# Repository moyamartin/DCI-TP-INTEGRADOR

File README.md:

## Trabajo práctico final de la asignatura DCI ##
Este repositorio contiene el trabajo práctico final para la asignatura de Diseño de Circuitos Impresos de la carrera de posgrado de FIUBA.

* Autor: Martin Moya
* Título corto del trabajo: Módulo PPG MAX30101
* Descripción: Rediseño miniaturizado del módulo MAX30101 de MikroElektronika (sensor óptico de pulso y oximetría PPG) para su integración en un reloj. El objetivo es reducir el tamaño de la placa conservando la función de medición de frecuencia cardíaca y SpO2 por I2C.
* Cursada: OCT-NOV-DIC 2026

## Licencia de este trabajo ##
Este trabajo se distribuye bajo la licencia de hardware abierto CERN-OHL-P v2 (CERN Open Hardware Licence Version 2 - Permissive).
El texto de la licencia debe colocarse en el directorio raíz (LICENSE).

## Estructura del TP FINAL ##

Se propone y se pide utilizar la siguiente estructura.

* doc: Toda la información sobre el circuito, principalmente de autoría o procesamiento propio. Por ejemplo:
  * Notas de ingeniería propias.
  * Notas de aplicación propias.
  * Estudios previos, estado del arte, resumen de las investigaciones.
  * Notas con cálculos.
  * Dibujos adicionales.
  * Fotos de los prototipos.
  * Presupuestos, cotizaciones.
* info: Toda la iformación recolectada, principalmente de terceros, como por ejemplo:
  * Hojas de datos.
  * Notas de aplicación.
  * Info de productos comerciales.
  * Info en internet.
* pcb: Archivos de diseño esquemático y pcb.

Dependiendo la magnitud del proyecto, tendremos más o menos información en estos directorios. 
Revisar los README.md en cada directorio para conocer las pautas de cada uno para este TP.

NOTA: El alumno puede y debe borrar de este archivo todo lo que considere necesario, por ejemplo las aclaraciones del docente y esta misma nota.

## Obligatorios para el TP Final ##
* doc/propuesta/README.md (con textos y links, formato markdown, a imágenes que deben estar en el mismo repo. Las imágenes son las que se piden en las pautas de TP).
* info/*.pdf (Se piden solo las hojas de datos de los componentes relevantes como circuitos integrados, conectores particulares, módulos, etc. No es necesario poner hojas de pasivos, discretos comunes, conectores estándar.)
* pcb/* (Acá va el proyecto KiCad, modelos 3D, bibliotecas particulares y archivos generados como BOM, gerbers, etc.). EVITE subir al git archivos temporales de KiCad. Se recomienda usar un .gitignore adecuado.
* El alumnos es libre de agregar otras cosas, pero siempre tenga en cuenta que el repositorio es público. Evitar colocar información personal o documentación confidencial.

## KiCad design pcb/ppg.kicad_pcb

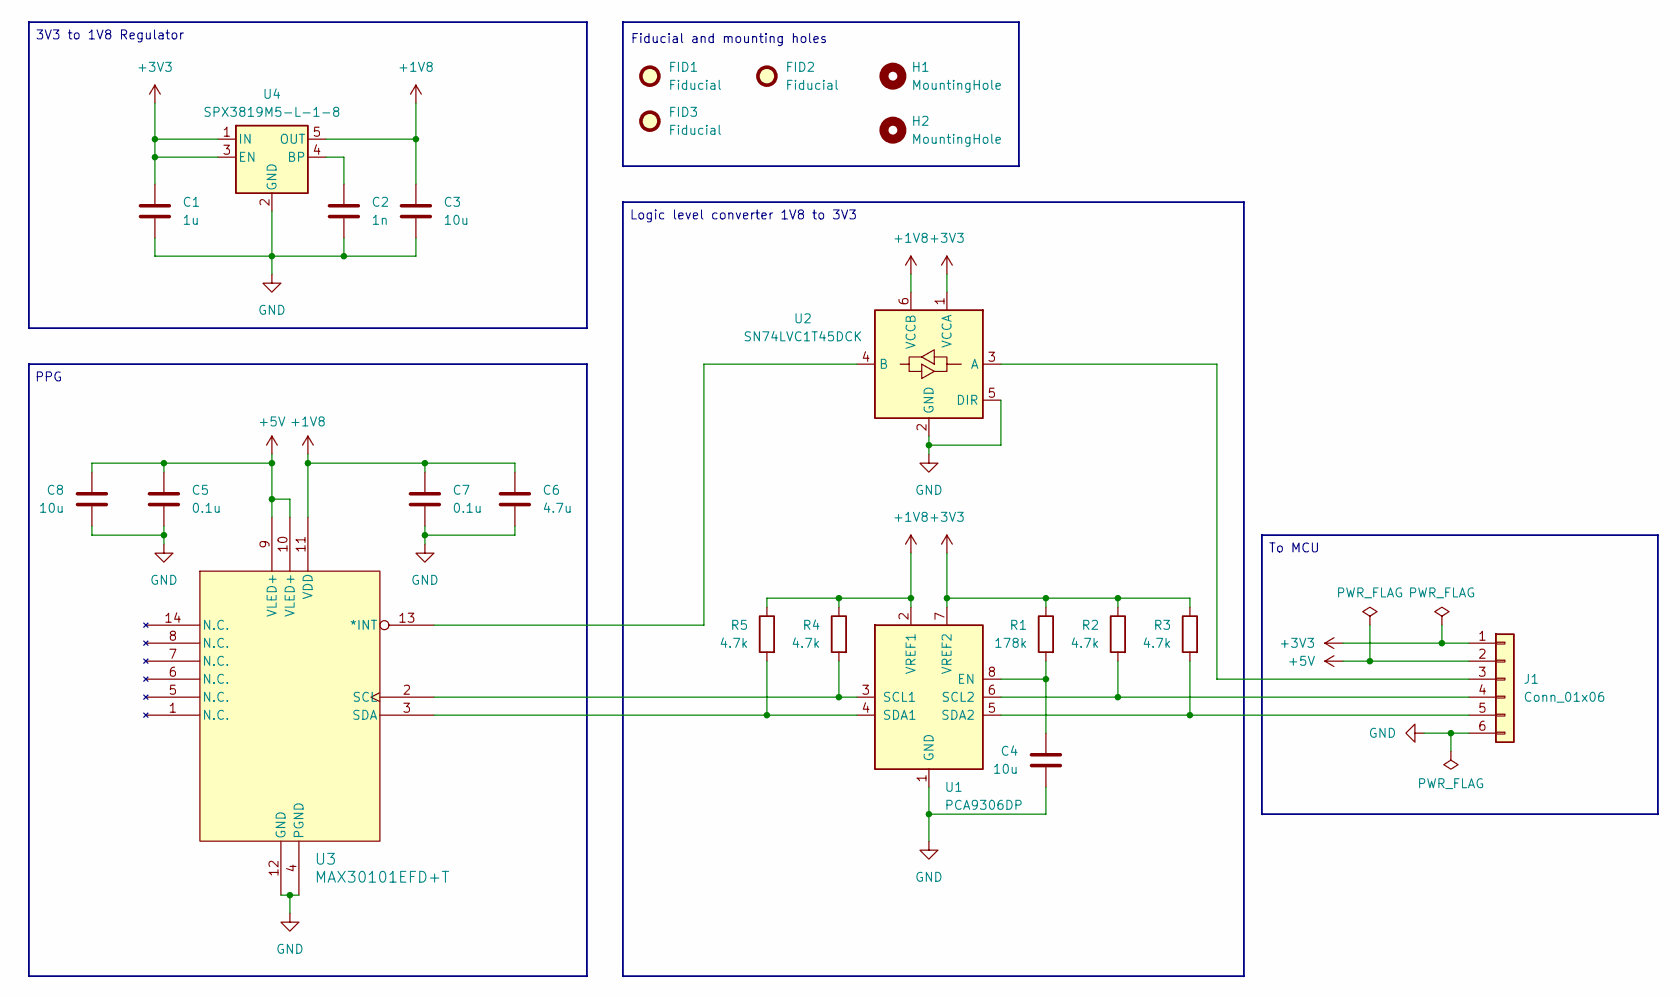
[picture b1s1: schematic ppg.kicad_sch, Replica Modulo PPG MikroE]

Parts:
C1: 1u; C_0603_1608Metric_Pad1.08x0.95mm_HandSolder; digikey# 399-C0603C104K5RACTUCT-ND
C2: 1n; C_0603_1608Metric_Pad1.08x0.95mm_HandSolder; digikey# 399-C0603X102K5RAC3316CT-ND
C3: 10u; C_0603_1608Metric_Pad1.08x0.95mm_HandSolder; digikey# 718-2355-1-ND
C4, C8: 10u; C_0603_1608Metric_Pad1.08x0.95mm_HandSolder; digikey# 1276-1869-1-ND
C5, C7: 0.1u; C_0603_1608Metric_Pad1.08x0.95mm_HandSolder; digikey# 399-C0603C104K5RACTUCT-ND
C6: 4.7u; C_0603_1608Metric_Pad1.08x0.95mm_HandSolder; digikey# 490-7203-1-ND
FID1, FID2, FID3: Fiducial; Fiducial_1mm_Mask2mm
H1, H2: MountingHole; MountingHole_2.1mm
J1: Conn_01x06; Molex_200528-0060_1x06-1MP_P1.00mm_Horizontal; digikey# WM24188CT-ND
R1: 178k; R_0603_1608Metric_Pad0.98x0.95mm_HandSolder; digikey# RMCF0603FT178KCT-ND
R2, R3, R4, R5: 4.7k; R_0603_1608Metric_Pad0.98x0.95mm_HandSolder; digikey# 311-4.70KHRCT-ND
U1: PCA9306DP; TSSOP-8_3x3mm_P0.65mm; digikey# 568-4243-1-ND
U2: SN74LVC1T45DCK; SOT-363_SC-70-6; digikey# 296-16844-1-ND
U3: MAX30101EFD+T; 21-1048F_F143A5&plus_1_MXM; digikey# MAX30101EFD+TCT-ND
U4: SPX3819M5-L-1-8; SOT-23-5; digikey# 1016-1411-ND

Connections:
+1V8: C3.1, C6.1, C7.1, R4.1, R5.1, U1.2 (VREF1), U2.6 (VCCB), U3.11 (VDD), U4.5 (OUT)
+3V3: C1.1, J1.1, R1.1, R2.1, R3.1, U1.7 (VREF2), U2.1 (VCCA), U4.1 (IN), U4.3 (EN)
+5V: C5.1, C8.1, J1.2, U3.9 (VLED+), U3.10 (VLED+)
GND: C1.2, C2.2, C3.2, C4.2, C5.2, C6.2, C7.2, C8.2, J1.6, U1.1 (GND), U2.2 (GND), U2.5 (DIR), U3.4 (PGND), U3.12 (GND), U4.2 (GND)
unnamed: J1.3, U2.3 (A)
unnamed: J1.4, R2.2, U1.6 (SCL2)
unnamed: J1.5, R3.2, U1.5 (SDA2)
unnamed: C4.1, R1.2, U1.8 (EN)
unnamed: R4.2, U1.3 (SCL1), U3.2 (SCL)
unnamed: R5.2, U1.4 (SDA1), U3.3 (SDA)
unnamed: U2.4 (B), U3.13 (*INT)
unnamed: C2.1, U4.4 (BP)

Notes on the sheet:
PPG
Logic level converter 1V8 to 3V3
3V3 to 1V8 Regulator
To MCU
Fiducial and mounting holes

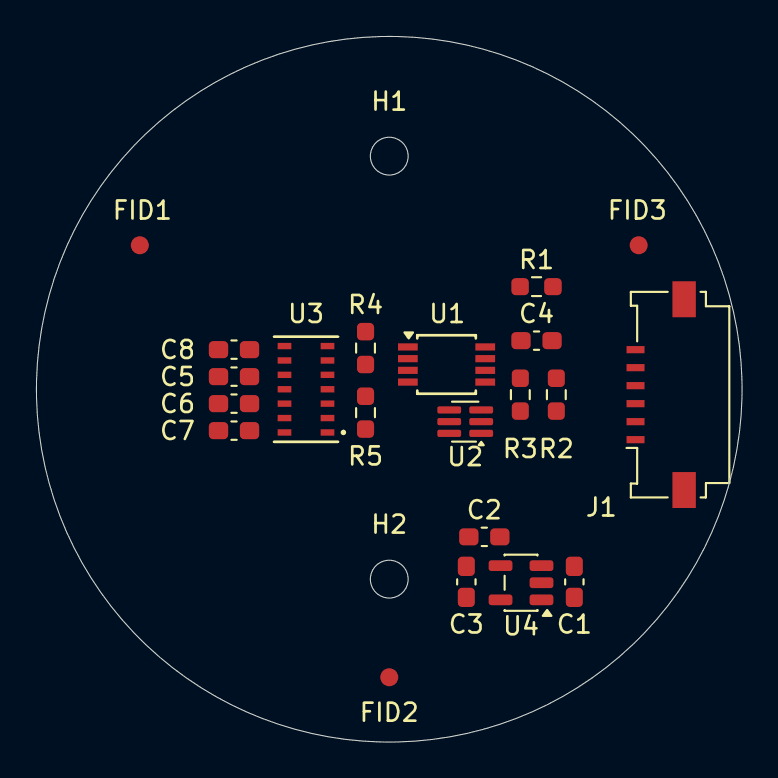
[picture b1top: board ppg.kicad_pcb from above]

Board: 2 copper layers, 39.2 x 39.2 mm, 23 parts (0 on the bottom side), 12 nets.

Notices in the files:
pcb/ppg.kicad_sch:
License: CERN-OHL-P V2
